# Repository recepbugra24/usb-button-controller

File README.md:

# USB Button Controller

A minimal USB HID keyboard board that reads two externally wired buttons and
sends keystrokes to a host computer. No drivers required — the host enumerates
it as a standard keyboard.

Designed around the WCH CH552G, an 8-bit MCU with an integrated USB device
controller, on-chip 24 MHz oscillator and on-chip 5 V to 3.3 V regulator. This
removes the crystal, load capacitors, reset network and programming header that
a comparable AVR design would need, and cuts the controller cost from roughly
$4.70 to $0.31 per unit.

An interactive version is in `docs/3d-viewer.html` (open it in a browser).

## Specifications

| | |
|---|---|
| MCU | WCH CH552G (SOP-16) |
| Interface | USB 2.0 Full Speed, USB-C connector |
| Inputs | 2 buttons, wired off-board via screw terminal |
| Power | Bus powered, ~20 mA |
| Board | 41.8 × 25.25 mm, 2 layers, 1.6 mm FR-4 |
| Assembly | Single sided (top), SMD |

## Design notes

**USB.** Both differential pairs of the USB-C receptacle are tied together so
the cable works in either orientation. CC1 and CC2 each carry a 5.1 kΩ pulldown
to advertise the board as a sink; without them the host supplies no power.
A USBLC6-2SC6 clamps ESD on D+/D- as close to the connector as layout allows.

**Button inputs.** Each channel has a 4.7 kΩ pull-up so the input never floats,
a 1 kΩ series resistor and a 100 nF capacitor forming a low-pass filter with a
0.1 ms time constant, and a second USBLC6-2SC6 protecting against discharge
carried in on the button wiring. The filter suppresses contact bounce in
hardware; firmware adds a short debounce window on top.

**Programming.** The CH552G ships with a USB bootloader in ROM. Holding SW1
while plugging in pulls D+ to V33 through a 10 kΩ resistor, which puts the chip
into bootloader mode. No external programmer is needed.

**Ground.** Copper pours on both layers, stitched with vias. The pour under the
USB pair is kept unbroken to hold the differential impedance steady.

## Repository layout

```
usb-button-controller.kicad_sch     schematic
usb-button-controller.kicad_pcb     board layout
usb-button-controller.kicad_pro     project file
docs/                   isometric render and interactive 3D viewer
gerber/                 fabrication output
  *.gtl *.gbl           copper layers
  *.gts *.gbs           solder mask
  *.gto *.gbo           silkscreen
  *.gm1                 board outline
  *.drl                 drill file
  BOM_jlcpcb.csv        bill of materials with LCSC part numbers
  usb-button-controller-all-pos.csv component placement
```

## Manufacturing

Built for JLCPCB with assembly. Upload the gerber archive, then the BOM and
placement files from `gerber/`.

Settings: 2 layers, 1.6 mm, HASL, top-side assembly. Enable **Confirm Parts
Placement** — KiCad and JLCPCB do not always agree on the zero-rotation
reference for SOT-23 and SOP packages, and the preview is where a misoriented
part gets caught.

All passives, the LED and the tactile switch are JLCPCB Basic parts. The
CH552G, USB-C receptacle, USBLC6-2SC6 and screw terminal are Extended parts and
carry a per-part setup fee.

## Firmware

Built with [ch55xduino](https://github.com/DeqingSun/ch55xduino) in the Arduino
IDE. Add this board manager URL:

```
https://raw.githubusercontent.com/DeqingSun/ch55xduino/ch55xduino/package_ch55xduino_mcs51_index.json
```

Install **CH55x Boards**, select **CH552 Board**, and pick a USB setting that
reserves RAM for HID. Pin mapping:

| Function | Port | Arduino pin |
|---|---|---|
| Button 1 | P3.3 | 33 |
| Button 2 | P3.4 | 34 |
| Status LED | P1.7 | 17 |

A blank chip enters the bootloader on its own, so the first upload needs no
button press. Later uploads are triggered automatically unless the running
firmware has locked up the USB stack, in which case hold SW1 and replug.

## Verification

- ERC clean
- DRC clean, zero unconnected items
- Schematic parity between board and schematic confirmed
- Netlist reviewed pin by pin against the CH552G datasheet

Not yet verified in hardware — no board has been built from these files.

## License

Not yet chosen. Add a LICENSE file before sharing this publicly.

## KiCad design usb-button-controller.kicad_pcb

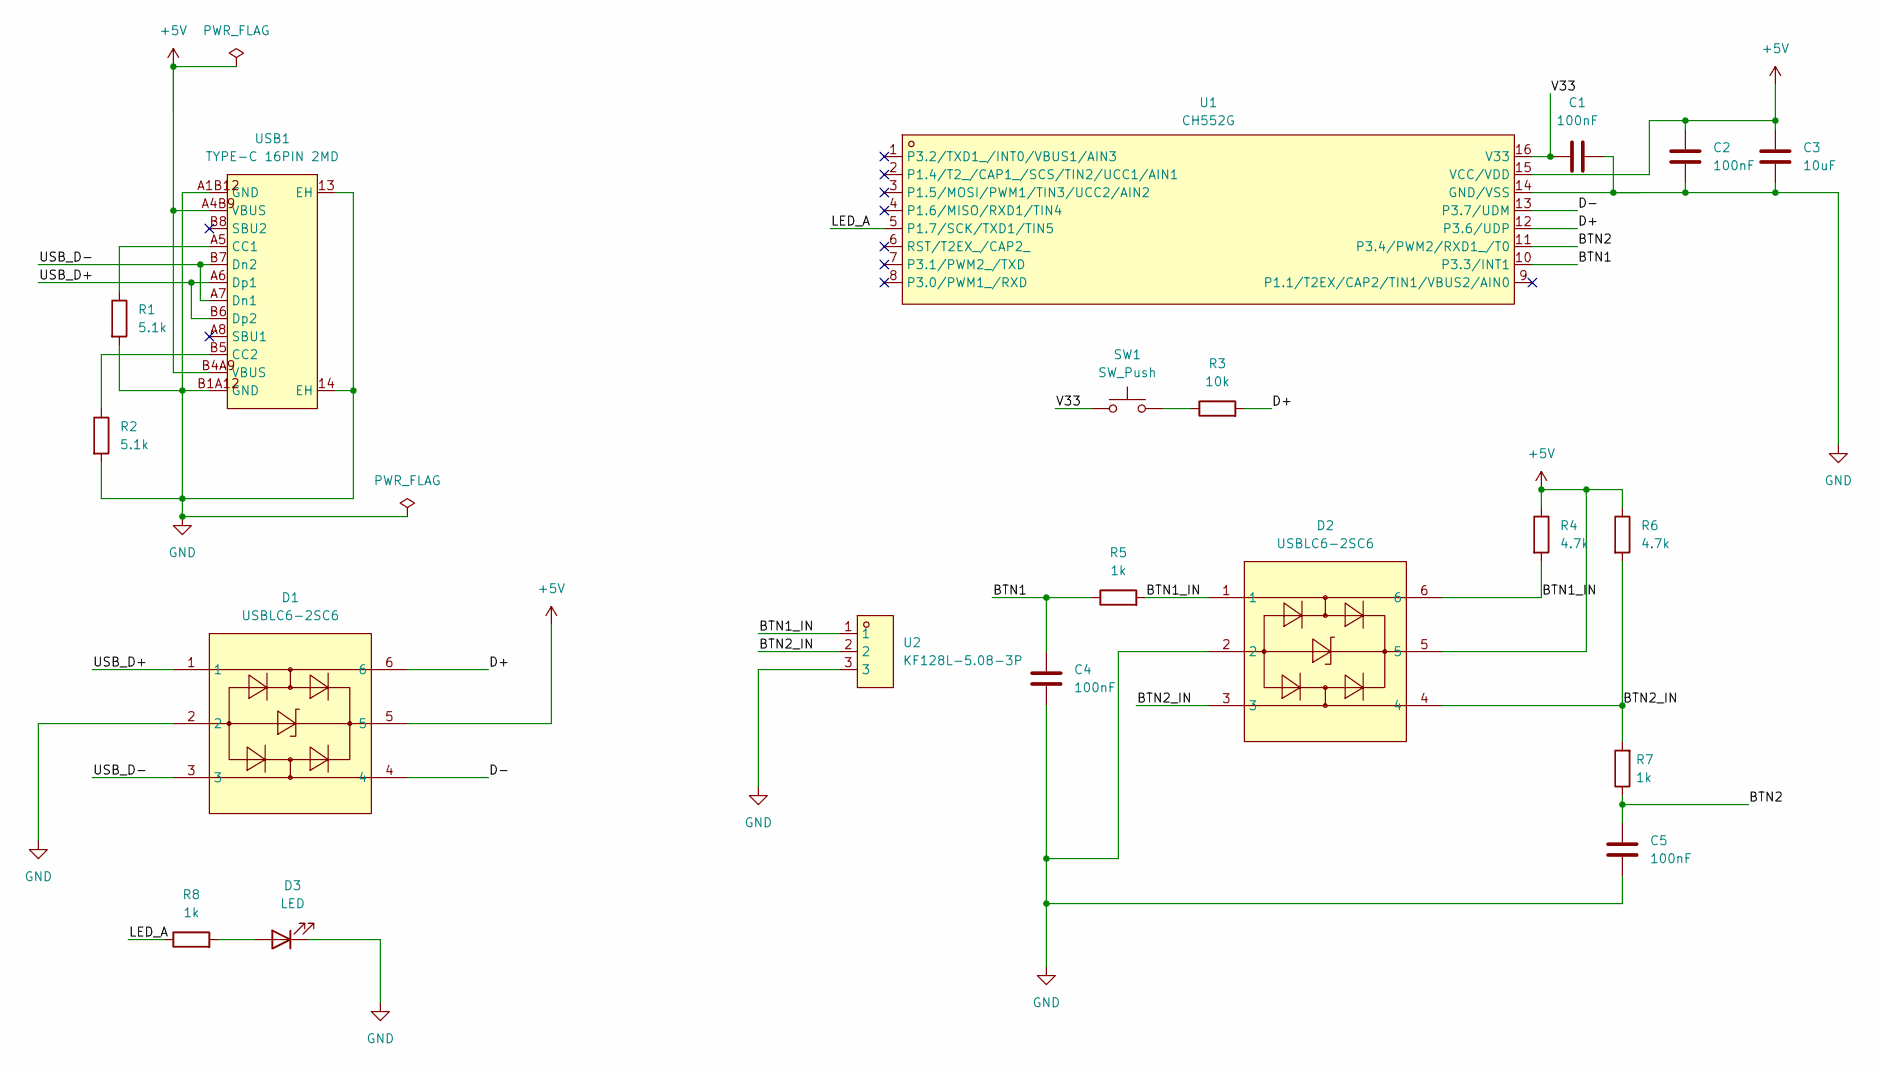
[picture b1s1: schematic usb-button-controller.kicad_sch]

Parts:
C1, C2, C4: 100nF; C_0603_1608Metric
C3: 10uF; C_0603_1608Metric
C5: 100nF; C_0805_2012Metric
D1, D2: USBLC6-2SC6; SOT-23-6_L2.9-W1.6-P0.95-LS2.8-BL; MPN USBLC6-2SC6; LCSC Part C7519
D3: LED; LED_0603_1608Metric
R1, R2: 5.1k; R_0603_1608Metric
R3: 10k; R_0603_1608Metric
R4, R6: 4.7k; R_0603_1608Metric
R5, R7, R8: 1k; R_0603_1608Metric
SW1: SW_Push; SW_SPST_TL3342
U1: CH552G; SOP-16_L10.0-W3.9-P1.27-LS6.0-BL; MPN CH552G; LCSC Part C111292
U2: KF128L-5.08-3P; CONN-TH_3P-P5.08_KF128L-5.08-3P; MPN KF128L-5.08-3P; LCSC Part C474941
USB1: TYPE-C 16PIN 2MD; USB-C-SMD_TYPE-C-16PIN-2MD-073; MPN TYPE-C 16PIN 2MD(073); LCSC Part C2765186

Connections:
+5V: C2.1, C3.1, D1.5, D2.5, R4.1, R6.1, U1.15 (VCC/VDD), USB1.A4B9 (VBUS), USB1.B4A9 (VBUS)
/BTN1: C4.1, R5.1, U1.10 (P3.3/INT1)
/BTN1_IN: D2.1, D2.6, R4.2, R5.2, U2.1
/BTN2: C5.1, R7.1, U1.11 (P3.4/PWM2/RXD1_/T0)
/BTN2_IN: D2.3, D2.4, R6.2, R7.2, U2.2
/D+: D1.6, R3.2, U1.12 (P3.6/UDP)
/D-: D1.4, U1.13 (P3.7/UDM)
/LED_A: R8.1, U1.5 (P1.7/SCK/TXD1/TIN5)
/USB_D+: D1.1, USB1.A6 (Dp1), USB1.B6 (Dp2)
/USB_D-: D1.3, USB1.A7 (Dn1), USB1.B7 (Dn2)
/V33: C1.1, SW1.1, U1.16 (V33)
GND: C1.2, C2.2, C3.2, C4.2, C5.2, D1.2, D2.2, D3.1 (K), R1.2, R2.2, U1.14 (GND/VSS), U2.3, USB1.13 (EH), USB1.14 (EH), USB1.A1B12 (GND), USB1.B1A12 (GND)
unnamed: D3.2 (A), R8.2
unnamed: R3.1, SW1.2
unnamed: R1.1, USB1.A5 (CC1)
unnamed: R2.1, USB1.B5 (CC2)

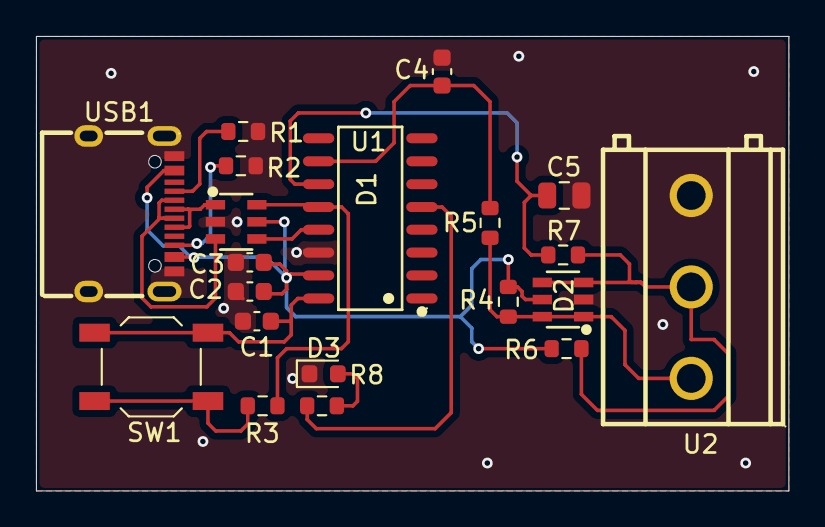
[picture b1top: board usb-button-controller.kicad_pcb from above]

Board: 2 copper layers, 41.8 x 25.2 mm, 20 parts (0 on the bottom side), 16 nets.

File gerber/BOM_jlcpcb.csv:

Comment,Designator,Footprint,JLCPCB Part #
CH552G,U1,SOP-16,C111292
TYPE-C 16PIN 2MD(073),USB1,USB-C-SMD-16P,C2765186
USBLC6-2SC6,"D1,D2",SOT-23-6,C7519
KF128L-5.08-3P,U2,KF128-3P-5.08,C474941
100nF,"C1,C2,C4",0603,C14663
100nF,C5,0805,C49678
10uF,C3,0603,C19702
5.1k,"R1,R2",0603,C23186
4.7k,"R4,R6",0603,C23162
1k,"R5,R7,R8",0603,C21190
10k,R3,0603,C25804
LED red,D3,0603,C2286
Tact switch,SW1,SW_SPST_TL3342,C318884
